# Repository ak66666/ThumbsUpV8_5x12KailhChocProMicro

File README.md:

# ThumbsUp! v8 5x12 Keyboard for Kailh Choc and Gateron Low Profile switches dirven by ProMicro and pin-compatibles

Multilevel 58 Key Ergonomic Contoured Mechanical Keyboard.

The board uses Kailh Choc and Gateron Low Profile Switches with hot-swap sockets.

ProMicro or pin-compatible MCUs are supported, including Raspberry RP2040 with [QMK, see this fork.](https://github.com/ak66666/qmk_firmware/tree/thumbsup_20240523/keyboards/thumbsup)

Supports Proglide Cirque touchpad (up to 40mm diameter).

Can be made wireless with nice!nano v2 and a battery, [ZMK firmware.](https://github.com/ak66666/zmk-config/tree/master)

# Photos

Black PCBs - v8 with Kailh Choc switches, PCBs are 1.6mm thick
Red PCBs - v8b with Gateron Low Profile switches, PCB thickness is 1.2mm, GLP switch pins are too short (or rather are tapered at the ends too much), what creates poor/unstable contact with the sockets in 1.6mm PCBs.

v8 with Kailh Choc Blue switches

ThumbsUp! v2 and v8

ThumbsUp! v8 and v5

# Firmware
The default firmware is here:

# Here you can buy it

# More info

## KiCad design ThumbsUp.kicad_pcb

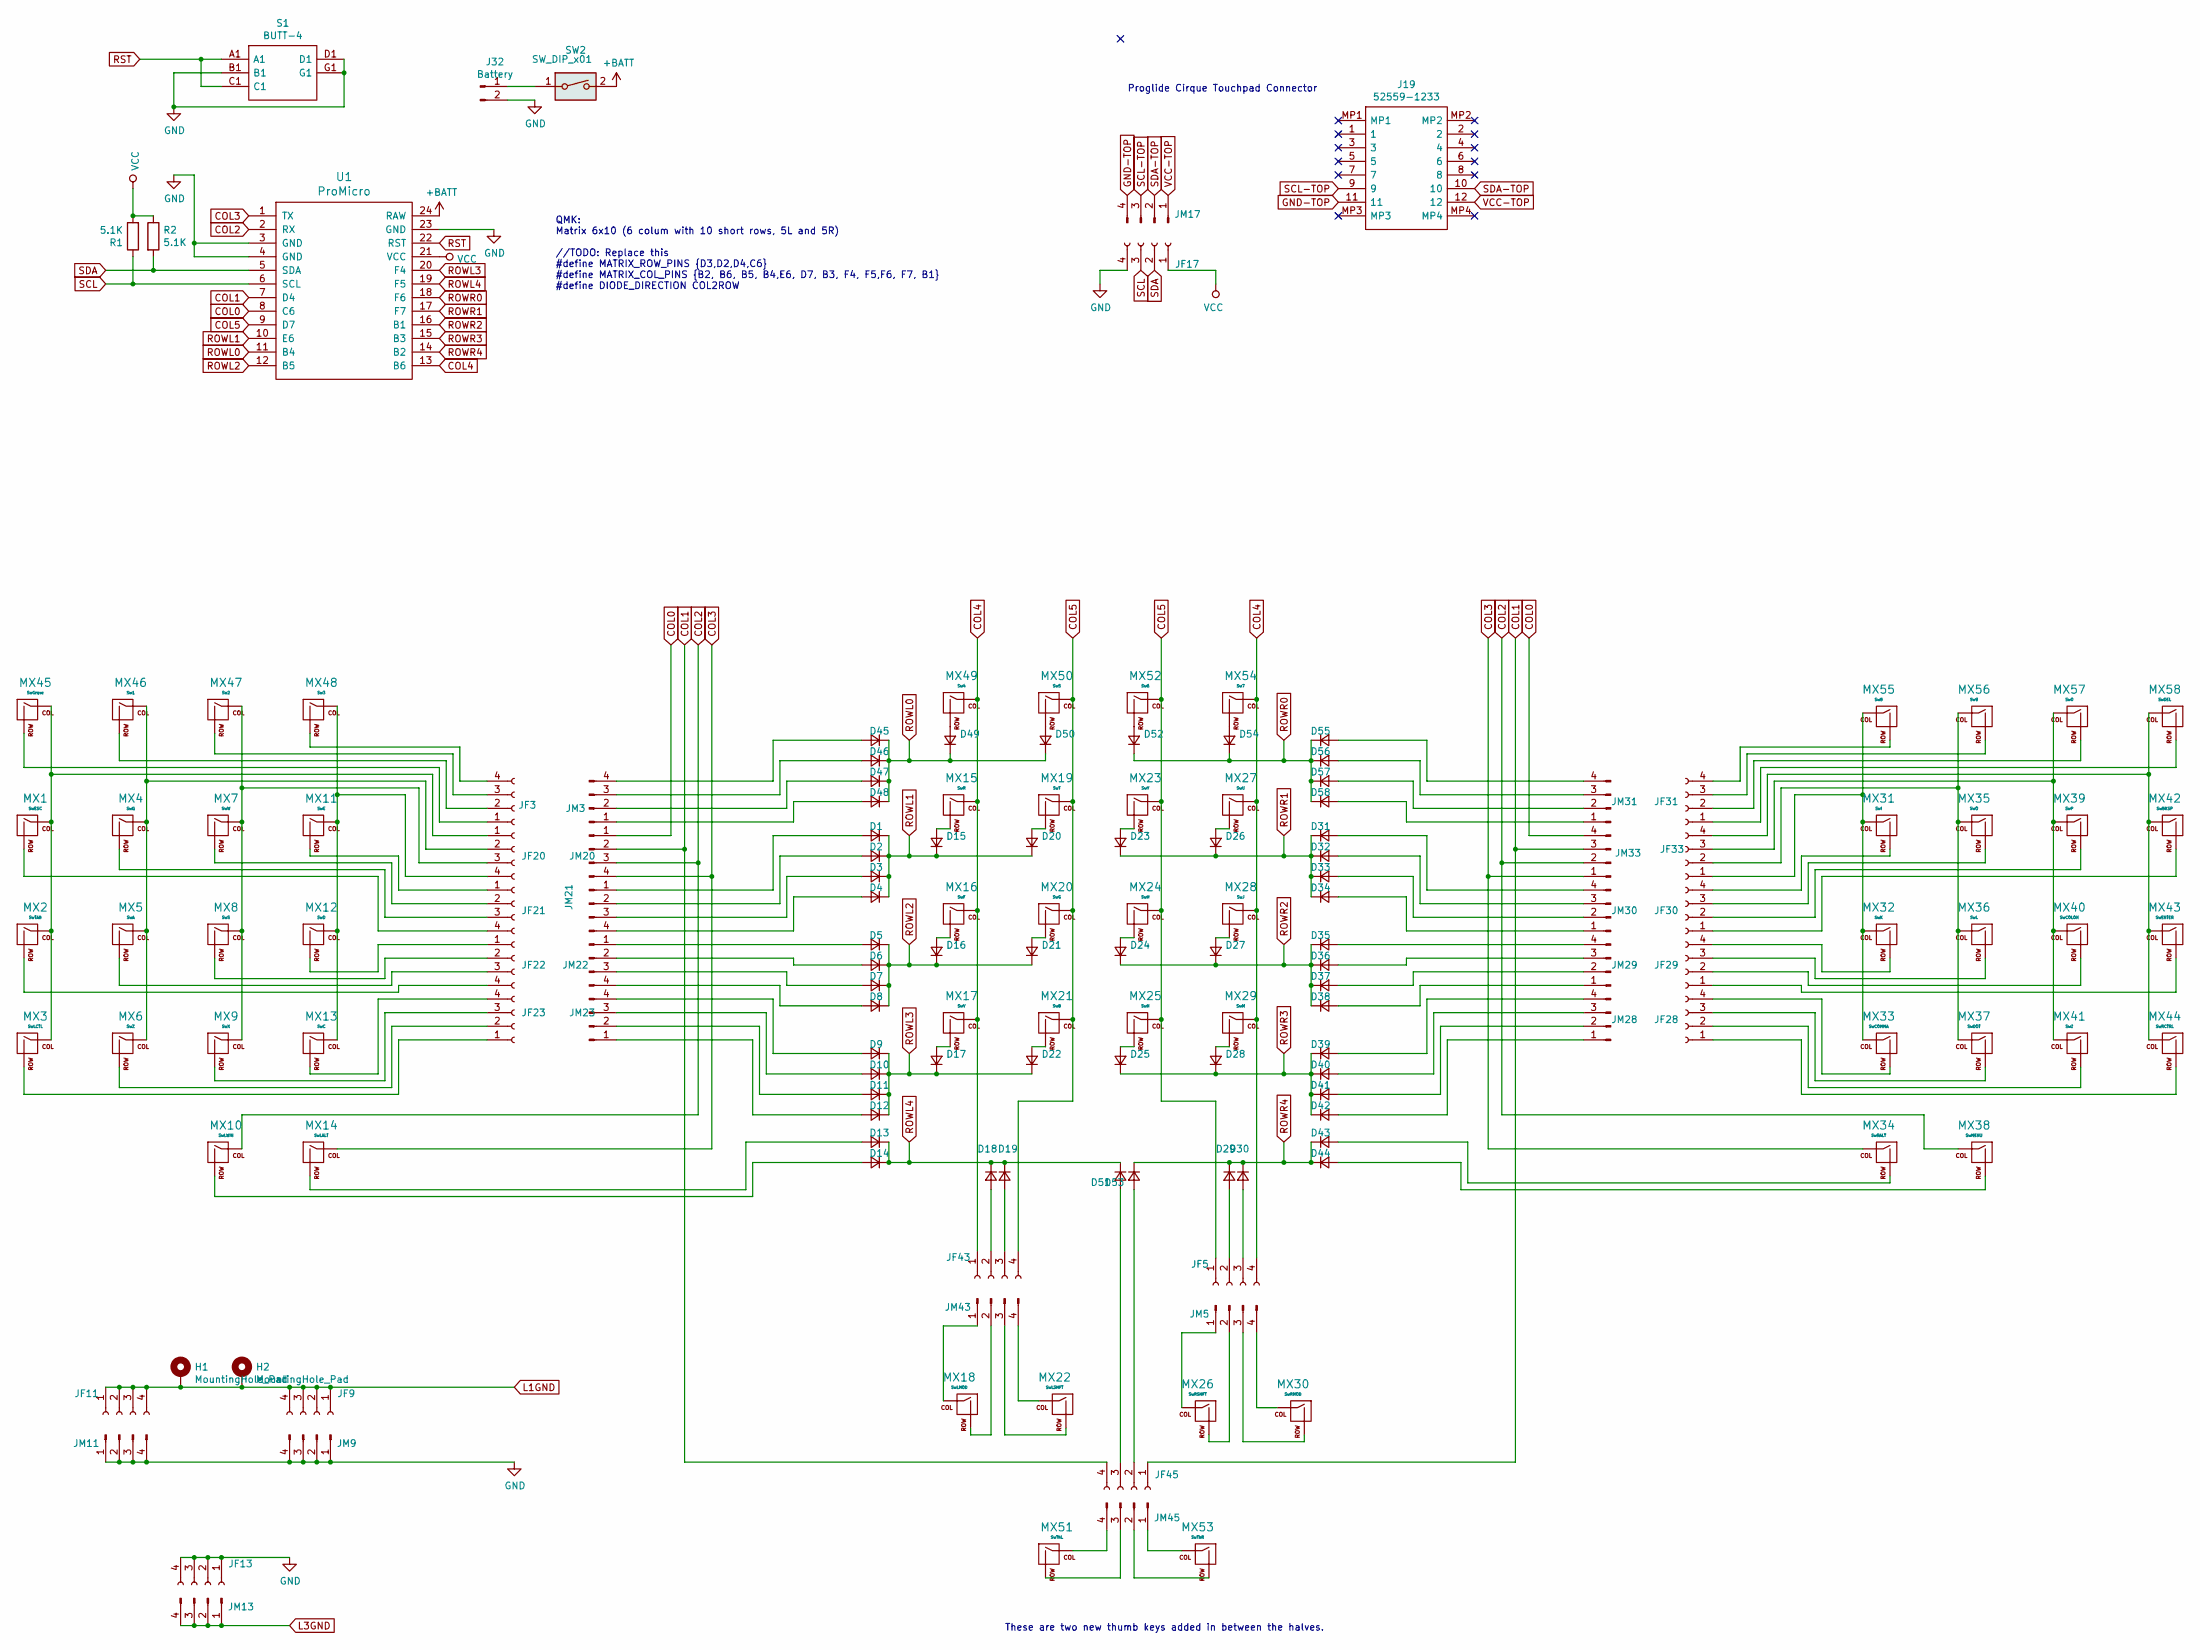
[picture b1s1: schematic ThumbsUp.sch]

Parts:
D1, D2, D3, D4, D5, D6, D7, D8, D9, D10, D11, D12, D13, D14, D15, D16, D17, D18, D19, D20, D21, D22, D23, D24, D25, D26, D27, D28, D29, D30, D31, D32, D33, D34, D35, D36, D37, D38, D39, D40, D41, D42, D43, D44, D45, D46, D47, D48, D49, D50, D51, D52, D53, D54, D55, D56, D57, D58: D_Small; D_SOD-123
H1: MountingHole_Pad; MountingHole_6mm_Pad_Via
H2: MountingHole_Pad; MountingHole_8.4mm_M8_Pad_Via
J19: 52559-1233; 525591233; Mouser Part Number 538-52559-1233
J32: Battery; PinHeader_1x02_P2.54mm_Vertical
JF3, JF5, JF20, JF21, JF22, JF23, JF28, JF29, JF30, JF31, JF33, JF43, JF45: Conn_01x04_Female; PinSocket_1x04_P2.54mm_Vertical
JF9, JF11, JF13, JF17: Raiser_Female; PinSocket_1x04_P2.54mm_Vertical
JM3, JM20, JM21, JM22, JM23, JM28, JM29, JM30, JM31, JM33, JM43, JM45: Conn_01x04_Male; PinHeader_1x04_P2.54mm_Vertical
JM5: Male; PinHeader_1x04_P2.54mm_Vertical
JM9, JM11, JM13, JM17: Raiser_Male; PinHeader_1x04_P2.54mm_Vertical
MX1: SwESC; PG1350_GLv2
MX2: SwTAB; PG1350_GLv2
MX3: SwLCTL; PG1350_GLv2
MX4: SwQ; PG1350_GLv2
MX5: SwA; PG1350_GLv2
MX6: SwZ; PG1350_GLv2
MX7: SwW; PG1350_GLv2
MX8: SwS; PG1350_GLv2
MX9: SwX; PG1350_GLv2
MX10: SwLWIN; PG1350_GLv2
MX11: SwE; PG1350_GLv2
MX12: SwD; PG1350_GLv2
MX13: SwC; PG1350_GLv2
MX14: SwLALT; PG1350_GLv2
MX15: SwR; PG1350_GLv2
MX16: SwF; PG1350_GLv2
MX17: SwV; PG1350_GLv2
MX18: SwLMOD; PG1350_GLv2
MX19: SwT; PG1350_GLv2
MX20: SwG; PG1350_GLv2
MX21: SwB; PG1350_GLv2
MX22: SwLSHFT; PG1350_GLv2
MX23: SwY; PG1350_GLv2
MX24: SwH; PG1350_GLv2
MX25: SwN; PG1350_GLv2
MX26: SwRSHFT; PG1350_GLv2
MX27: SwU; PG1350_GLv2
MX28: SwJ; PG1350_GLv2
MX29: SwM; PG1350_GLv2
MX30: SwRMOD; PG1350_GLv2
MX31: SwI; PG1350_GLv2
MX32: SwK; PG1350_GLv2
MX33: SwCOMMA; PG1350_GLv2
MX34: SwRALT; PG1350_GLv2
MX35: SwO; PG1350_GLv2
MX36: SwL; PG1350_GLv2
MX37: SwDOT; PG1350_GLv2
MX38: SwMENU; PG1350_GLv2
MX39: SwP; PG1350_GLv2
MX40: SwCOLON; PG1350_GLv2
MX41: Sw?; PG1350_GLv2
MX42: SwBKSP; PG1350_GLv2
MX43: SwENTER; PG1350_GLv2
MX44: SwRCTRL; PG1350_GLv2
MX45: SwGrave; PG1350_GLv2
MX46: Sw1; PG1350_GLv2
MX47: Sw2; PG1350_GLv2
MX48: Sw3; PG1350_GLv2
MX49: Sw4; PG1350_GLv2
MX50: Sw5; PG1350_GLv2
MX51: SwThL; PG1350_GLv2
MX52: Sw6; PG1350_GLv2
MX53: SwThR; PG1350_GLv2
MX54: Sw7; PG1350_GLv2
MX55: Sw8; PG1350_GLv2
MX56: Sw9; PG1350_GLv2
MX57: Sw0; PG1350_GLv2
MX58: SwDEL; PG1350_GLv2
R1, R2: 5.1K; R_0805_2012Metric
S1: BUTT-4; BUTT4; Manufacturer_Part_Number BUTT-4; Mouser Part Number 992-BUTT-4
SW2: SW_DIP_x01; 18252321
U1: ProMicro

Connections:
+BATT: SW2.2, U1.24 (RAW)
COL0: JM20.1, JM33.4, U1.8 (C6)
COL1: JF45.1, JF45.4, JM20.2, JM33.3, U1.7 (D4)
COL2: JM20.3, JM33.2, MX10.1 (COL), MX38.1 (COL), U1.2 (RX)
COL3: JM20.4, JM33.1, MX14.1 (COL), MX34.1 (COL), U1.1 (TX)
COL4: JF5.4, JF43.1, MX15.1 (COL), MX16.1 (COL), MX17.1 (COL), MX27.1 (COL), MX28.1 (COL), MX29.1 (COL), MX49.1 (COL), MX54.1 (COL), U1.13 (B6)
COL5: JF5.1, JF43.4, MX19.1 (COL), MX20.1 (COL), MX21.1 (COL), MX23.1 (COL), MX24.1 (COL), MX25.1 (COL), MX50.1 (COL), MX52.1 (COL), U1.9 (D7)
GND: J32.2, JF13.1, JF13.2, JF13.3, JF13.4, JF17.4, JM9.1, JM9.2, JM9.3, JM9.4, JM11.1, JM11.2, JM11.3, JM11.4, S1.B1, S1.D1, S1.G1, U1.3 (GND), U1.4 (GND), U1.23 (GND)
GND-TOP: J19.11, JM17.4
L1GND: H1.1, H2.1, JF9.1, JF9.2, JF9.3, JF9.4, JF11.1, JF11.2, JF11.3, JF11.4
L3GND: JM13.1, JM13.2, JM13.3, JM13.4
unnamed: D1.2 (A), JM21.1
unnamed: D2.2 (A), JM21.2
unnamed: D3.2 (A), JM21.3
unnamed: D4.2 (A), JM21.4
unnamed: D5.2 (A), JM22.1
unnamed: D6.2 (A), JM22.2
unnamed: D7.2 (A), JM22.3
unnamed: D8.2 (A), JM22.4
unnamed: D9.2 (A), JM23.4
unnamed: D10.2 (A), JM23.3
unnamed: D11.2 (A), JM23.2
unnamed: D12.2 (A), JM23.1
unnamed: D13.2 (A), MX14.2 (ROW)
unnamed: D14.2 (A), MX10.2 (ROW)
unnamed: D15.2 (A), MX15.2 (ROW)
unnamed: D16.2 (A), MX16.2 (ROW)
unnamed: D17.2 (A), MX17.2 (ROW)
unnamed: D18.2 (A), JF43.2
unnamed: D19.2 (A), JF43.3
unnamed: D20.2 (A), MX19.2 (ROW)
unnamed: D21.2 (A), MX20.2 (ROW)
unnamed: D22.2 (A), MX21.2 (ROW)
unnamed: D23.2 (A), MX23.2 (ROW)
unnamed: D24.2 (A), MX24.2 (ROW)
unnamed: D25.2 (A), MX25.2 (ROW)
unnamed: D26.2 (A), MX27.2 (ROW)
unnamed: D27.2 (A), MX28.2 (ROW)
unnamed: D28.2 (A), MX29.2 (ROW)
unnamed: D29.2 (A), JF5.2
unnamed: D30.2 (A), JF5.3
unnamed: D31.2 (A), JM30.4
unnamed: D32.2 (A), JM30.3
unnamed: D33.2 (A), JM30.2
unnamed: D34.2 (A), JM30.1
unnamed: D35.2 (A), JM29.4
unnamed: D36.2 (A), JM29.3
unnamed: D37.2 (A), JM29.2
unnamed: D38.2 (A), JM29.1
unnamed: D39.2 (A), JM28.4
unnamed: D40.2 (A), JM28.3
unnamed: D41.2 (A), JM28.2
unnamed: D42.2 (A), JM28.1
unnamed: D43.2 (A), MX34.2 (ROW)
unnamed: D44.2 (A), MX38.2 (ROW)
unnamed: D45.2 (A), JM3.4
unnamed: D46.2 (A), JM3.3
unnamed: D47.2 (A), JM3.2
unnamed: D48.2 (A), JM3.1
unnamed: D49.2 (A), MX49.2 (ROW)
unnamed: D50.2 (A), MX50.2 (ROW)
unnamed: D51.2 (A), JF45.3
unnamed: D52.2 (A), MX52.2 (ROW)
unnamed: D53.2 (A), JF45.2
unnamed: D54.2 (A), MX54.2 (ROW)
unnamed: D55.2 (A), JM31.4
unnamed: D56.2 (A), JM31.3
unnamed: D57.2 (A), JM31.2
unnamed: D58.2 (A), JM31.1
unnamed: J32.1, SW2.1
unnamed: JF3.1, MX45.2 (ROW)
unnamed: JF3.2, MX46.2 (ROW)
unnamed: JF3.3, MX47.2 (ROW)
unnamed: JF3.4, MX48.2 (ROW)
unnamed: JF20.1, MX1.1 (COL), MX2.1 (COL), MX3.1 (COL), MX45.1 (COL)
unnamed: JF20.2, MX4.1 (COL), MX5.1 (COL), MX6.1 (COL), MX46.1 (COL)
unnamed: JF20.3, MX7.1 (COL), MX8.1 (COL), MX9.1 (COL), MX47.1 (COL)
unnamed: JF20.4, MX11.1 (COL), MX12.1 (COL), MX13.1 (COL), MX48.1 (COL)
unnamed: JF21.1, MX11.2 (ROW)
unnamed: JF21.2, MX7.2 (ROW)
unnamed: JF21.3, MX4.2 (ROW)
unnamed: JF21.4, MX1.2 (ROW)
unnamed: JF22.1, MX12.2 (ROW)
unnamed: JF22.2, MX8.2 (ROW)
unnamed: JF22.3, MX5.2 (ROW)
unnamed: JF22.4, MX2.2 (ROW)
unnamed: JF23.1, MX3.2 (ROW)
unnamed: JF23.2, MX6.2 (ROW)
unnamed: JF23.3, MX9.2 (ROW)
unnamed: JF23.4, MX13.2 (ROW)
unnamed: JF28.1, MX44.2 (ROW)
unnamed: JF28.2, MX41.2 (ROW)
unnamed: JF28.3, MX37.2 (ROW)
unnamed: JF28.4, MX33.2 (ROW)
unnamed: JF29.1, MX43.2 (ROW)
unnamed: JF29.2, MX40.2 (ROW)
unnamed: JF29.3, MX36.2 (ROW)
unnamed: JF29.4, MX32.2 (ROW)
unnamed: JF30.1, MX42.2 (ROW)
unnamed: JF30.2, MX39.2 (ROW)
unnamed: JF30.3, MX35.2 (ROW)
unnamed: JF30.4, MX31.2 (ROW)
unnamed: JF31.1, MX58.2 (ROW)
unnamed: JF31.2, MX57.2 (ROW)
unnamed: JF31.3, MX56.2 (ROW)
unnamed: JF31.4, MX55.2 (ROW)
unnamed: JF33.1, MX31.1 (COL), MX32.1 (COL), MX33.1 (COL), MX55.1 (COL)
unnamed: JF33.2, MX35.1 (COL), MX36.1 (COL), MX37.1 (COL), MX56.1 (COL)
unnamed: JF33.3, MX39.1 (COL), MX40.1 (COL), MX41.1 (COL), MX57.1 (COL)
unnamed: JF33.4, MX42.1 (COL), MX43.1 (COL), MX44.1 (COL), MX58.1 (COL)
unnamed: JM5.1, MX26.1 (COL)
unnamed: JM5.2, MX26.2 (ROW)
unnamed: JM5.3, MX30.2 (ROW)
unnamed: JM5.4, MX30.1 (COL)
unnamed: JM43.1, MX18.1 (COL)
unnamed: JM43.2, MX18.2 (ROW)
unnamed: JM43.3, MX22.2 (ROW)
unnamed: JM43.4, MX22.1 (COL)
unnamed: JM45.1, MX53.1 (COL)
unnamed: JM45.2, MX53.2 (ROW)
unnamed: JM45.3, MX51.2 (ROW)
unnamed: JM45.4, MX51.1 (COL)
ROWL0: D45.1 (K), D46.1 (K), D47.1 (K), D48.1 (K), D49.1 (K), D50.1 (K), U1.11 (B4)
ROWL1: D1.1 (K), D2.1 (K), D3.1 (K), D4.1 (K), D15.1 (K), D20.1 (K), U1.10 (E6)
ROWL2: D5.1 (K), D6.1 (K), D7.1 (K), D8.1 (K), D16.1 (K), D21.1 (K), U1.12 (B5)
ROWL3: D9.1 (K), D10.1 (K), D11.1 (K), D12.1 (K), D17.1 (K), D22.1 (K), U1.20 (F4)
ROWL4: D13.1 (K), D14.1 (K), D18.1 (K), D19.1 (K), D51.1 (K), U1.19 (F5)
ROWR0: D52.1 (K), D54.1 (K), D55.1 (K), D56.1 (K), D57.1 (K), D58.1 (K), U1.18 (F6)
ROWR1: D23.1 (K), D26.1 (K), D31.1 (K), D32.1 (K), D33.1 (K), D34.1 (K), U1.17 (F7)
ROWR2: D24.1 (K), D27.1 (K), D35.1 (K), D36.1 (K), D37.1 (K), D38.1 (K), U1.16 (B1)
ROWR3: D25.1 (K), D28.1 (K), D39.1 (K), D40.1 (K), D41.1 (K), D42.1 (K), U1.15 (B3)
ROWR4: D29.1 (K), D30.1 (K), D43.1 (K), D44.1 (K), D53.1 (K), U1.14 (B2)
RST: S1.A1, S1.C1, U1.22 (RST)
SCL: JF17.3, R1.1, U1.6 (SCL)
SCL-TOP: J19.9, JM17.3
SDA: JF17.2, R2.2, U1.5 (SDA)
SDA-TOP: J19.10, JM17.2
VCC: JF17.1, R1.2, R2.1, U1.21 (VCC)
VCC-TOP: J19.12, JM17.1

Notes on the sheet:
QMK: Matrix 6x10 (6 colum with 10 short rows, 5L and 5R) //TODO: Replace this #define MATRIX_ROW_PINS {D3,D2,D4,C6} #define MATRIX_COL_PINS {B2, B6, B5, B4,E6, D7, B3, F4, F5,F6, F7, B1} #define DIODE_DIRECTION COL2ROW
Proglide Cirque Touchpad Connector
These are two new thumb keys added in between the halves.

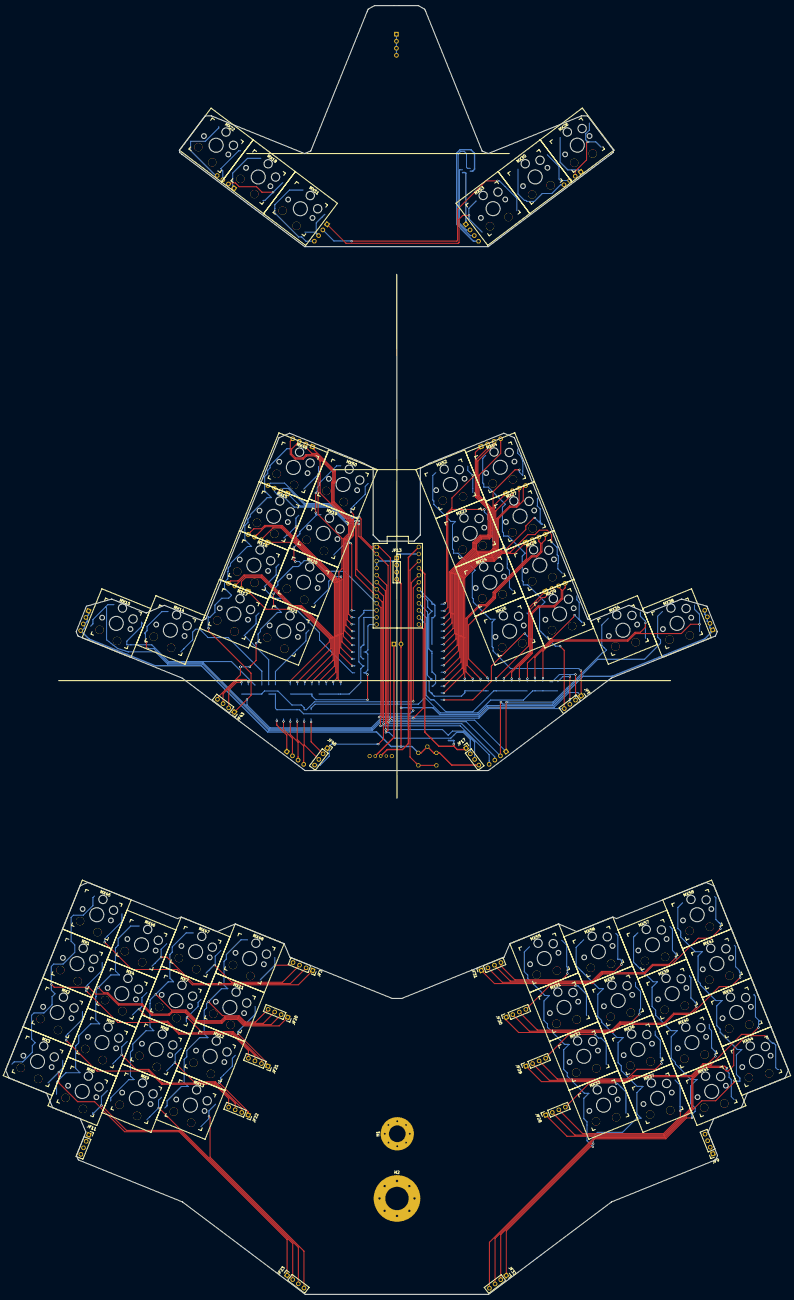
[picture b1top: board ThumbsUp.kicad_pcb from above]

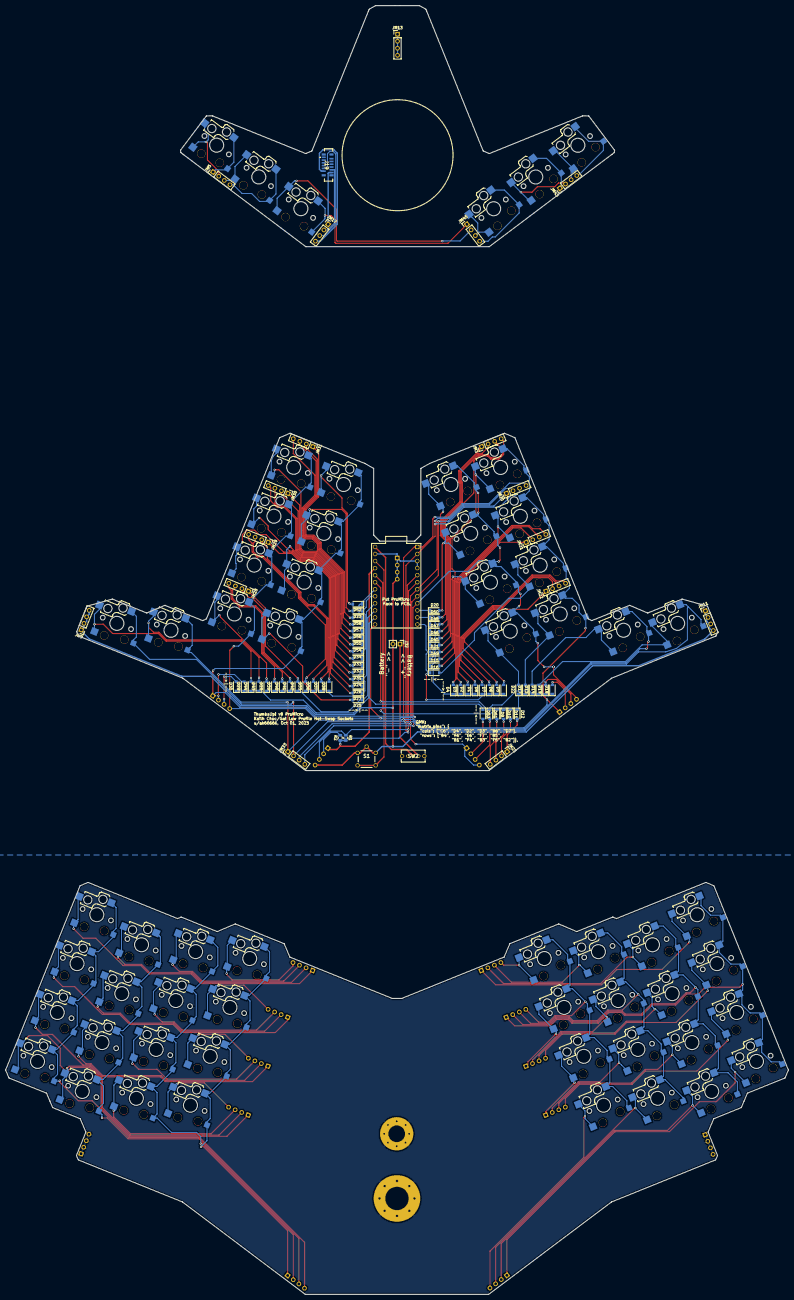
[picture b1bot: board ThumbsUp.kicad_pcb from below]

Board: 2 copper layers, 282.0 x 464.4 mm, 159 parts (81 on the bottom side), 139 nets.

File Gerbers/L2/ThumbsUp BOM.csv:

"Id";"Designator";"Package";"Quantity";"Designation";"Supplier and ref";
1;"D58,D7,D6,D20,D28,D22,D32,D11,D25,D38,D40,D13,D16,D44,D46,D26,D35,D27,D9,D12,D14,D15,D19,D1,D3,D2,D4,D5,D8,D17,D10,D18,D21,D23,D24,D29,D30,D31,D33,D34,D36,D37,D39,D41,D42,D43,D45,D47,D50,D52,D53,D54,D51,D55,D56,D49,D57,D48";"D_SOD-123";58;"D_Small";;;
2;"R1,R2";"R_0805_2012Metric";2;"5.1K";;;
3;"JM30,JM29,JM22,JM21,JM3,JM20,JM31,JM28,JM33,JM23";"PinHeader_1x04_P2.54mm_Vertical";10;"Conn_01x04_Male";;;
4;"SW2";"18252321";1;"SW_DIP_x01";;;
5;"JM9,JM11";"PinHeader_1x04_P2.54mm_Vertical";2;"Raiser_Male";;;
6;"J32";"PinHeader_1x02_P2.54mm_Vertical";1;"Battery";;;
7;"JF13,JF17";"PinSocket_1x04_P2.54mm_Vertical";2;"Raiser_Female";;;
8;"S1";"BUTT4";1;"BUTT-4";;;
9;"MX16";"PG1350_GLv2";1;"SwF";;;
10;"MX23";"PG1350_GLv2";1;"SwY";;;
11;"MX21";"PG1350_GLv2";1;"SwB";;;
12;"MX34";"PG1350_GLv2";1;"SwRALT";;;
13;"MX28";"PG1350_GLv2";1;"SwJ";;;
14;"U1";"ProMicro";1;"ProMicro";;;
15;"MX38";"PG1350_GLv2";1;"SwMENU";;;
16;"MX29";"PG1350_GLv2";1;"SwM";;;
17;"MX19";"PG1350_GLv2";1;"SwT";;;
18;"MX14";"PG1350_GLv2";1;"SwLALT";;;
19;"MX15";"PG1350_GLv2";1;"SwR";;;
20;"MX24";"PG1350_GLv2";1;"SwH";;;
21;"MX20";"PG1350_GLv2";1;"SwG";;;
22;"MX25";"PG1350_GLv2";1;"SwN";;;
23;"MX17";"PG1350_GLv2";1;"SwV";;;
24;"MX27";"PG1350_GLv2";1;"SwU";;;
25;"MX10";"PG1350_GLv2";1;"SwLWIN";;;
26;"MX49";"PG1350_GLv2";1;"Sw4";;;
27;"MX50";"PG1350_GLv2";1;"Sw5";;;
28;"MX52";"PG1350_GLv2";1;"Sw6";;;
29;"MX54";"PG1350_GLv2";1;"Sw7";;;
30;"JF45,JF5,JF43";"PinSocket_1x04_P2.54mm_Vertical";3;"Conn_01x04_Female";;;
31;"G***";"Crowfeet";1;"LOGO";;;

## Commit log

2023-09-17 Initiated the v8
2023-09-23 Replaced the switch footprint
2023-09-26 Retraced the lower board
2023-10-01 Redefined the layout, checked in before splitting the layers.
2023-10-01 Split the PCBs
2023-10-01 Started tracing the secoh
2023-10-02 Fixed and moved the cross board connectors.
2023-10-02 Wired Level 2.
2023-10-03 Wired all levels
2023-10-05 Added silkscreens, minor corrections before Gerbers generation.
2023-10-05 Generated Gerbers, POS and BOM files.
2023-10-24 Corrected switch footprint for Gateron sockets
2023-11-05 Adjusted some tracks around moved holes. Removed switch boundary from the top silkscreen.
2024-10-13 Added a folder with v8, v8b photos
2024-10-13 Update README.md for v8, v8b
2025-02-27 ThumbsUp v8: Updated description.
